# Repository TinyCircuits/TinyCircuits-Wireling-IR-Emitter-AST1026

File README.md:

# TinyCircuits Wireling IR Emitter
# AST1026 Rev2

The design files are located under design_files/ for the TinyCircuits AST1026 Rev 2 PCB. This Wireling features an 880 nm IR LED and can be used with our 38kHz IR Receiver Wireling or other IR receivers (like television sets). 

Format is in Cadsoft Eagle format - Eagle version 6.2 was used for the original design.

For more infomation on this, check out the product page at TinyCircuits.com

# License:

Design by TinyCircuits.
All design files are released under the Creative Commons Attribution Share-Alike 3.0 License, see the following link for details: http://creativecommons.org/licenses/by-sa/3.0

All text above must be included in any redistribution or derived design

This project uses designs and concepts developed as part of the Arduino project and the LilyPad project.  The TinyCircuits design files themselves (schematics, PCB and libraries) are not directly derived from these works' design files and have been created new, however the concepts and basic architecture behind the TinyDuino and TinyLily products are derived and we thank the hard work of the organizations below for their contributions to open-source hardware:
  
Original Arduino Uno Design by Team Arduino

LilyPad Arduino Design by Leah Buechley and Sparkfun Electronics

Please support the open-source hardware community

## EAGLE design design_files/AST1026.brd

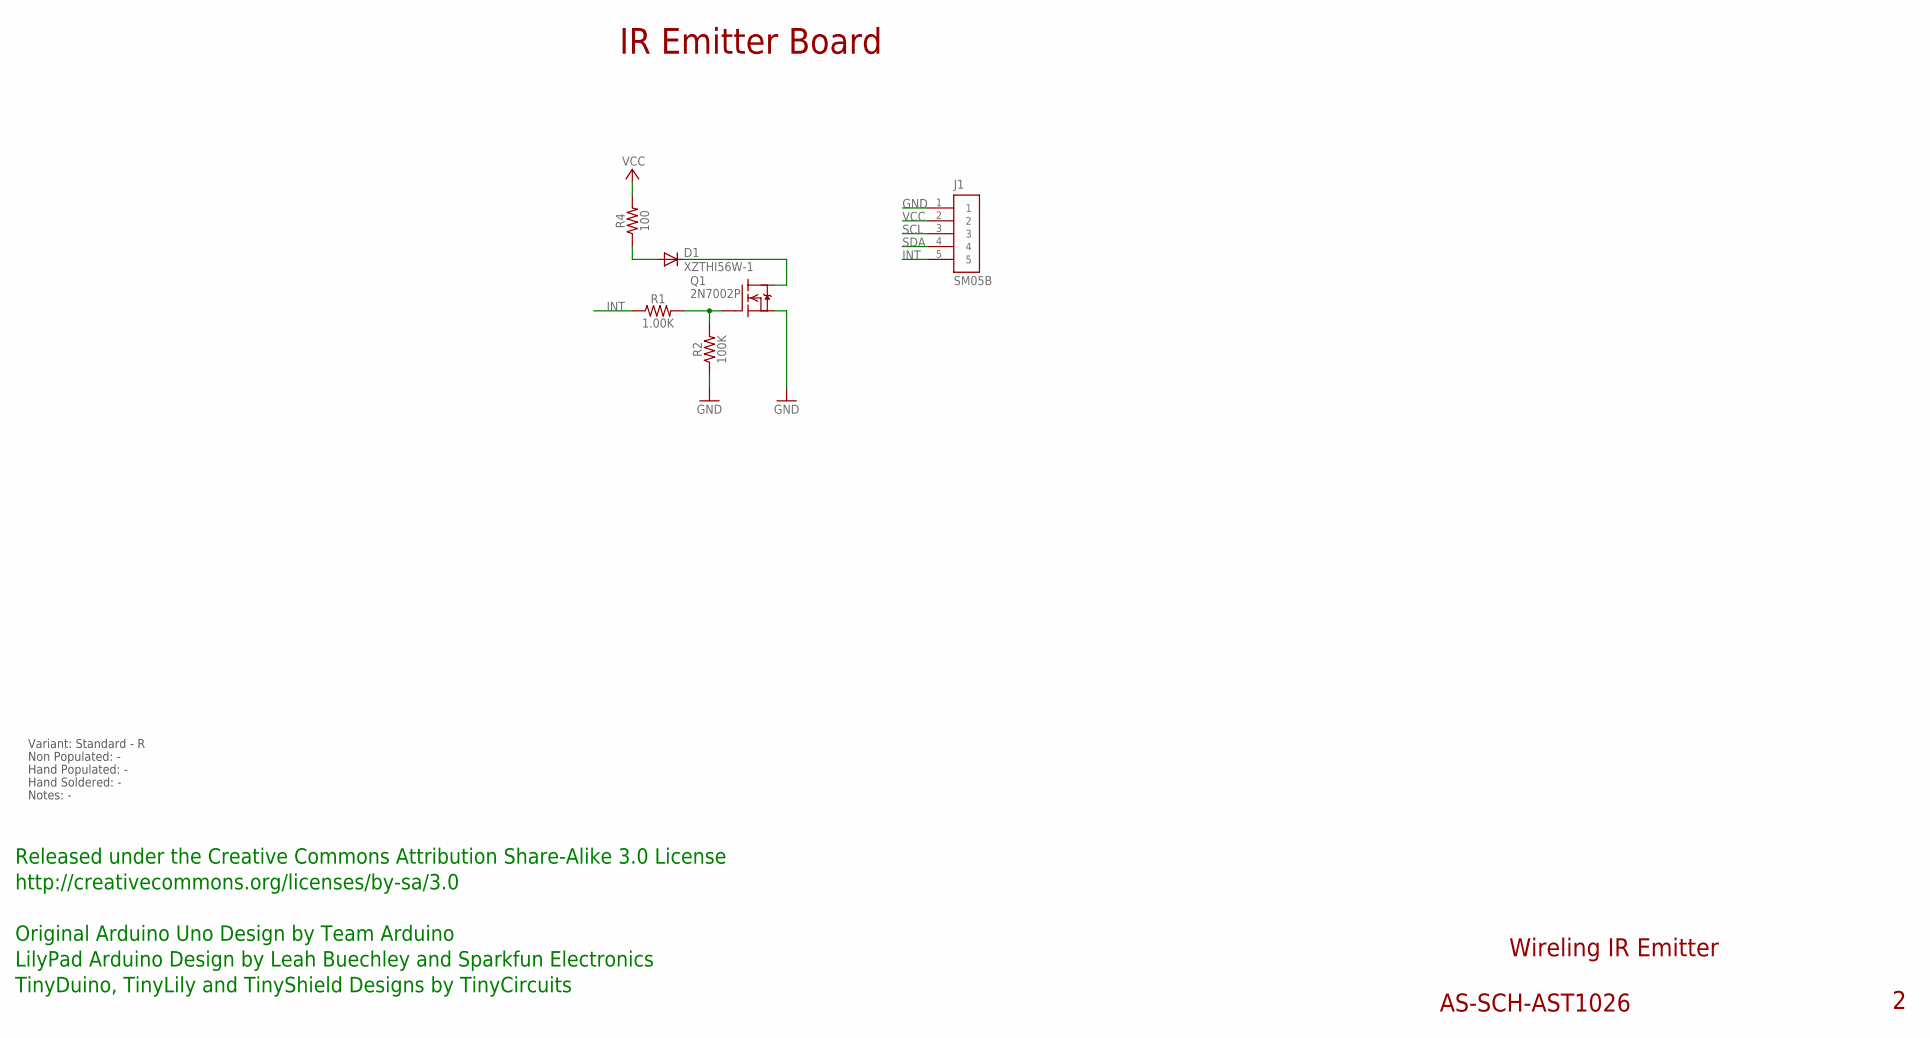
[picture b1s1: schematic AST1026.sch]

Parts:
D1: XZTHI56W-1; LED_SIDE_3.0X1.0; PARTNO AS-ITM-00551
J1: SM05B; JST_SH_5X1_EDGE
Q1: 2N7002P; SOT-416; PARTNO AS-ITM-00110
R1: 1.00K; 0402
R2: 100K; 0402
R4: 100; 0402

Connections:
GND: J1.1, Q1.2 (S), R2.1
INT: J1.5, R1.1
unnamed: D1.A, R4.1
unnamed: D1.C, Q1.3 (D)
unnamed: Q1.1 (G), R1.2, R2.2
SCL: J1.3
SDA: J1.4
VCC: J1.2, R4.2

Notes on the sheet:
Wireling IR Emitter
AS-SCH-AST1026
IR Emitter Board
Released under the Creative Commons Attribution Share-Alike 3.0 License
http://creativecommons.org/licenses/by-sa/3.0
Original Arduino Uno Design by Team Arduino
TinyDuino, TinyLily and TinyShield Designs by TinyCircuits
LilyPad Arduino Design by Leah Buechley and Sparkfun Electronics
Non Populated: -
Hand Populated: -
Hand Soldered: -
Notes: -
Variant: Standard - R

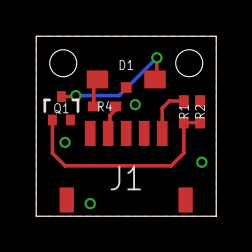
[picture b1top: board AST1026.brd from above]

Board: 2 copper layers, 10.0 x 10.0 mm, 7 parts (0 on the bottom side), 6 nets.

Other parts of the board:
U$1: DOCFIELD-TINYCIRCUITS-PCB

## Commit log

2019-11-20 init
2020-02-04 mass image update
2020-05-12 new code
2020-08-14 Add CAD data
